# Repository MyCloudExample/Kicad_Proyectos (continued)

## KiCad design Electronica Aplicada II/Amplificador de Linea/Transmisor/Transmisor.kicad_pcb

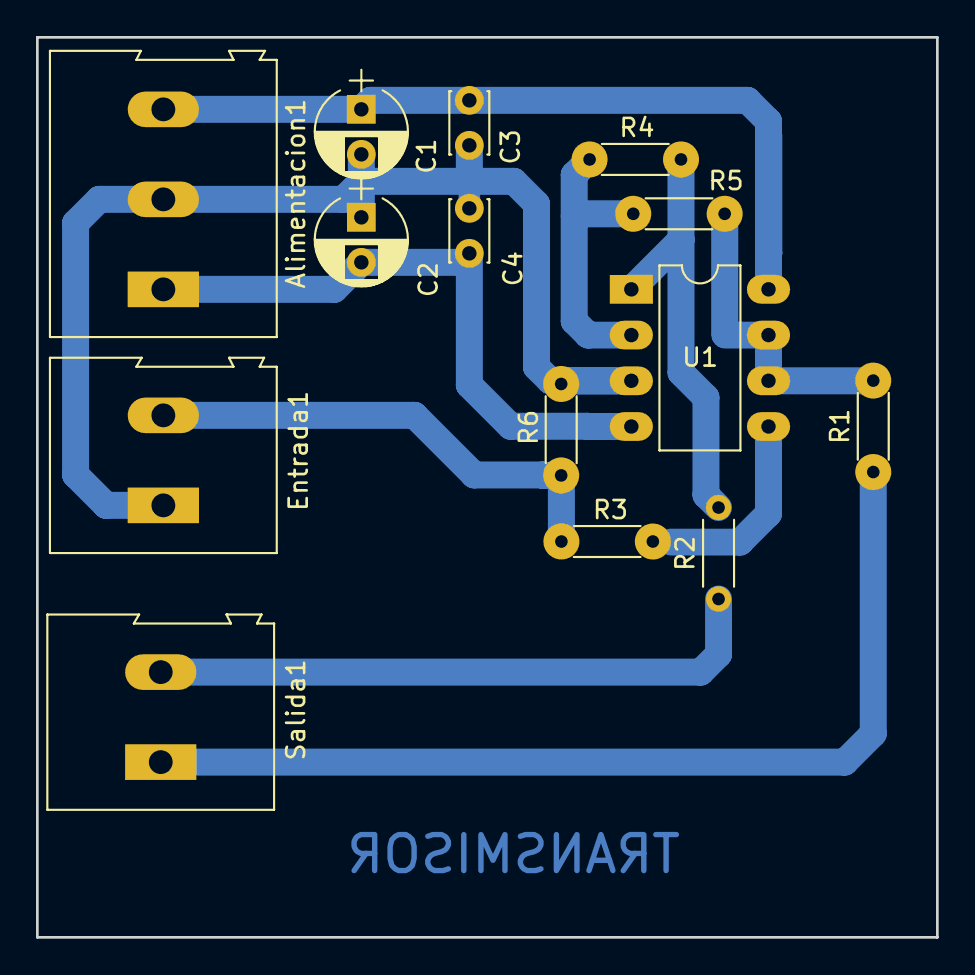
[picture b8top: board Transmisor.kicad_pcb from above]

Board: 2 copper layers, 50.0 x 50.0 mm, 14 parts (0 on the bottom side), 10 nets.

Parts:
Alimentacion1: -12V 0V +12V; TerminalBlock_Altech_AK300-3_P5.00mm
C1, C2: 100uF; CP_Radial_D5.0mm_P2.50mm
C3, C4: 0,1uF; C_Disc_D3.4mm_W2.1mm_P2.50mm
Entrada1: TerminalBlock_Altech_AK300-2_P5.00mm
R1, R2: 100; R_Axial_DIN0204_L3.6mm_D1.6mm_P5.08mm_Horizontal
R3: 1k; R_Axial_DIN0204_L3.6mm_D1.6mm_P5.08mm_Horizontal
R4, R5, R6: 10k; R_Axial_DIN0204_L3.6mm_D1.6mm_P5.08mm_Horizontal
Salida1: TerminalBlock_Altech_AK300-2_P5.00mm
U1: RC4558; DIP-8_W7.62mm_LongPads

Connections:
GNDREF: Alimentacion1.2, C1.2, C2.1, C3.1, C4.2, Entrada1.1, R6.1, U1.3
unnamed: Entrada1.2, R3.2, R6.2
unnamed: R1.1, Salida1.1
unnamed: R1.2, R4.2, U1.6, U1.7
unnamed: R2.1, Salida1.2
unnamed: R2.2, R5.1, U1.1
unnamed: R3.1, U1.5
unnamed: R4.1, R5.2, U1.2
VDD: Alimentacion1.3, C1.1, C3.2, U1.8
VSS: Alimentacion1.1, C2.2, C4.1, U1.4

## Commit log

2025-05-23 Carga Inicial de Proyectos Kicad
2025-05-26 Adicion de proyectos anteriores
2025-05-31 Actualizacion del Placa de Desarrollo 31/5/2025
2025-06-05 Agreggado de fuente al proyecto Placa_de_Desarrolo
2025-06-07 Placa_de_Desarrollo_7_6_2025
2025-06-07 Ignorar Backup del proyecto Placa_de_Desarrollo
2025-06-14 Actualizacion del proyecto Placa de Desarrollo 14_6_2025
2025-07-01 Actualizacion de Placa de Desarrollo, modificacionde pines
2025-08-13 Actualizacion de placa de prueba
2025-10-25 Actualizacion de respo Kicad
2025-12-13 Sin cambios reales
2025-12-23 Cambio de huella del Buzzer
2025-12-27 Mejora de Placa de desarrollo
2026-01-08 Version 1.0 finalizada
2026-01-10 Version 2.0 de la Placa de DEsarrollo
2026-01-12 Actualizacion de rama
2026-01-12 Limpieza de proyectos
2026-01-12 Borrado de proyecto Placa de DEsarrolo
2026-01-12 Limpieza de rama main
2026-01-12 Proyrcto definitivo de Placa de Desarrollo
2026-01-13 Prepraracion de rama main, para la creacion posterior de rama Placa_Desarrollo_Zero
2026-01-15 Version 1.0 de la placa de desarrollor para la Pico Zero
2026-01-18 Adicion de gitignore para Placa de desarrollo Pico Zero
2026-01-18 Remover carpeta de backups del rastreo de Git
2026-01-18 Adicion de gitignore para el proyecto Fuente 12V
2026-01-18 Adicion de gitignore y limpieza de indice
2026-01-18 Adicion de git ignore y limpieza de indice para el proyecto Placa de Desarrollo
2026-06-23 Resguardo para actualizar KiCAD a version 10
